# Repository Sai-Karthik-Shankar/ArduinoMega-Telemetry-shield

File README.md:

# ArduinoMega-Telemetry-shield

## Description
A simple datalogger with an Arduino mega at the heart of it, and a modular plate where inexpensive off the shelf modules for various purposes can be mounted.

## Capabilites
- 3-axis Acceleration
- 3-axis Gyroscope
- 3-axis Magnetometer
- GPS Location sensor
- 2 Channel Frequency inputs
- Bluetooth
- WiFi tethering
- Realtime Storage in Particle Photon Cloud
- Serial output to Nextion Display Module

## Additionals
Bluetooth Datalogger mobile application can interface with the ESP8266 and store the data collected in a sorted CSV file at the selected baud-rate.

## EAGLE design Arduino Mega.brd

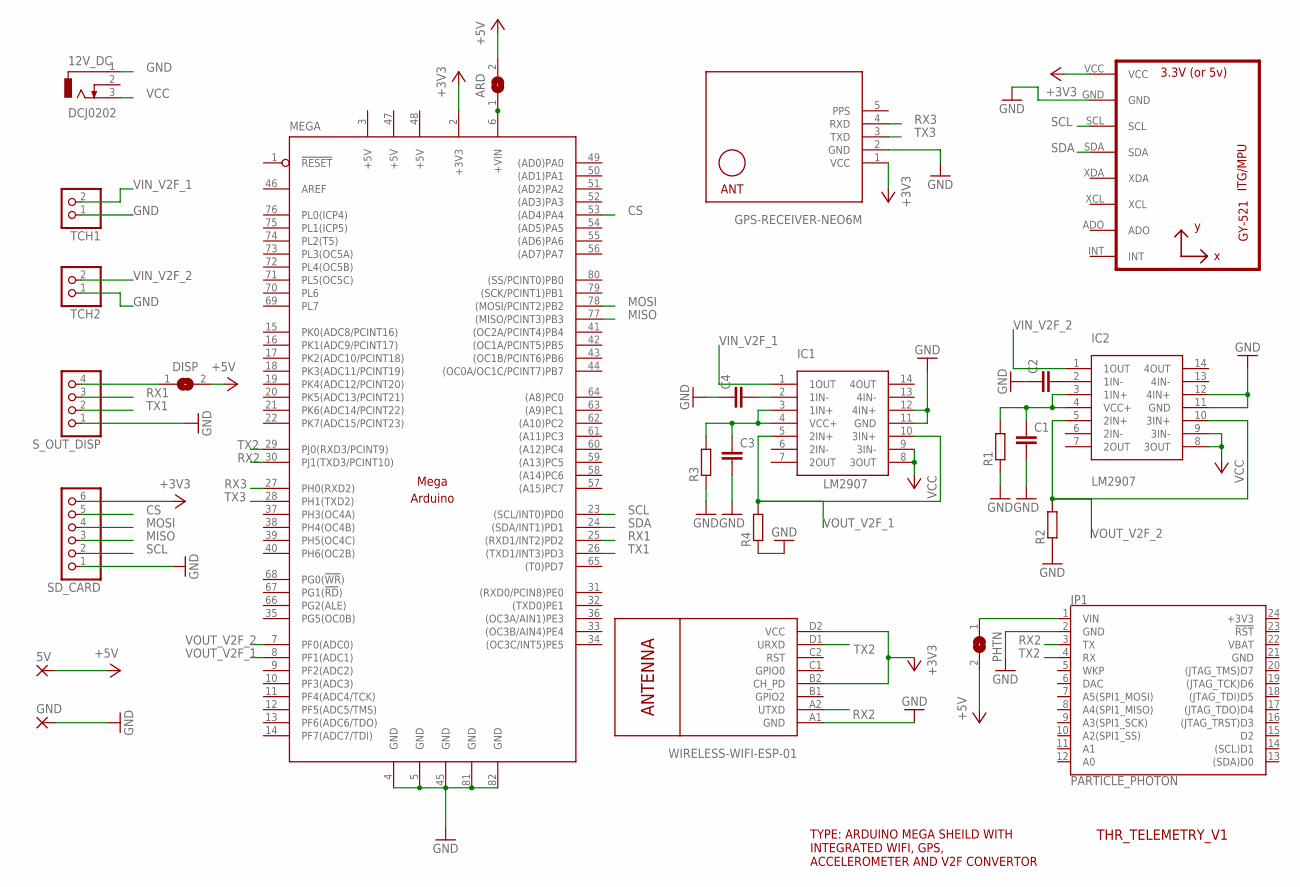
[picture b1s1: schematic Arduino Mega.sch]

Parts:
5V: WIREPADSMD5-2,5; 5-2,5
12V_DC: DCJ0202
ARD: SJ
C1, C2, C3, C4: C-EUC0805; C0805
DISP: SJ
GND: WIREPADSMD5-2,5; 5-2,5
IC1, IC2: LM2907; 14-SOIC
JP1: PARTICLE_PHOTON
MEGA: MEGAARDUINO_11; MEGA_ARDUINO_1
PHTN: SJ
R1, R2, R3, R4: R-EU_R0805; R0805
SD_CARD: PINHD-1X6; 1X06
S_OUT_DISP: PINHD-1X4; 1X04
TCH1, TCH2: PINHD-1X2; 1X02
U1: GY-521MPU6050; GY-521
U$1: GPS-RECEIVER-NEO6M
U$2: WIRELESS-WIFI-ESP-01

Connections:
+3V3: JP1.24 (+3V3), MEGA.2 (+3V3), SD_CARD.6, U1.VCC, U$1.1 (VCC), U$2.B2 (CH_PD), U$2.D2 (VCC)
+5V: 5V.1, ARD.2, DISP.2, MEGA.3 (+5V), MEGA.47 (+5V), MEGA.48 (+5V), PHTN.2
CS: MEGA.53 ((AD4)PA4), SD_CARD.5
GND: 12V_DC.1, C1.2, C2.1, C3.2, C4.1, GND.1, IC1.11 (GND), IC1.12 (4IN+), IC2.11 (GND), IC2.12 (4IN+), JP1.2 (GND), JP1.21 (GND), MEGA.4 (GND), MEGA.5 (GND), MEGA.45 (GND), MEGA.81 (GND), MEGA.82 (GND), R1.1, R2.1, R3.1, R4.1, SD_CARD.1, S_OUT_DISP.1, TCH1.1, TCH2.1, U1.GND, U$1.2 (GND), U$2.A1 (GND)
MISO: MEGA.77 ((MISO/PCINT3)PB3), SD_CARD.3
MOSI: MEGA.78 ((MOSI/PCINT2)PB2), SD_CARD.4
unnamed: C2.2, IC2.2 (1IN-)
unnamed: C1.1, IC2.3 (1IN+), IC2.4 (VCC+), R1.2
unnamed: ARD.1, MEGA.6 (+VIN)
unnamed: JP1.1 (VIN), PHTN.1
unnamed: C4.2, IC1.2 (1IN-)
unnamed: DISP.1, S_OUT_DISP.4
unnamed: C3.1, IC1.3 (1IN+), IC1.4 (VCC+), R3.2
PPS: U$1.5 (PPS)
RX1: MEGA.25 ((RXD1/INT2)PD2), S_OUT_DISP.3
RX2: JP1.3 (TX), MEGA.30 (PJ1(TXD3/PCINT10)), U$2.A2 (UTXD)
RX3: MEGA.27 (PH0(RXD2)), U$1.4 (RXD)
SCL: MEGA.23 ((SCL/INT0)PD0), SD_CARD.2, U1.SCL
SDA: MEGA.24 ((SDA/INT1)PD1), U1.SDA
TX1: MEGA.26 ((TXD1/INT3)PD3), S_OUT_DISP.2
TX2: JP1.4 (RX), MEGA.29 (PJ0(RXD3/PCINT9)), U$2.D1 (URXD)
TX3: MEGA.28 (PH1(TXD2)), U$1.3 (TXD)
VBAT: JP1.22 (VBAT)
VCC: 12V_DC.3, IC1.8 (3OUT), IC1.9 (3IN-), IC2.8 (3OUT), IC2.9 (3IN-)
VIN_V2F_1: IC1.1 (1OUT), TCH1.2
VIN_V2F_2: IC2.1 (1OUT), TCH2.2
VOUT_V2F_1: IC1.5 (2IN+), IC1.10 (3IN+), MEGA.8 (PF1(ADC1)), R4.2
VOUT_V2F_2: IC2.5 (2IN+), IC2.10 (3IN+), MEGA.7 (PF0(ADC0)), R2.2

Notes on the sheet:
THR_TELEMETRY_V1
TYPE: ARDUINO MEGA SHEILD WITH INTEGRATED WIFI, GPS, ACCELEROMETER AND V2F CONVERTOR

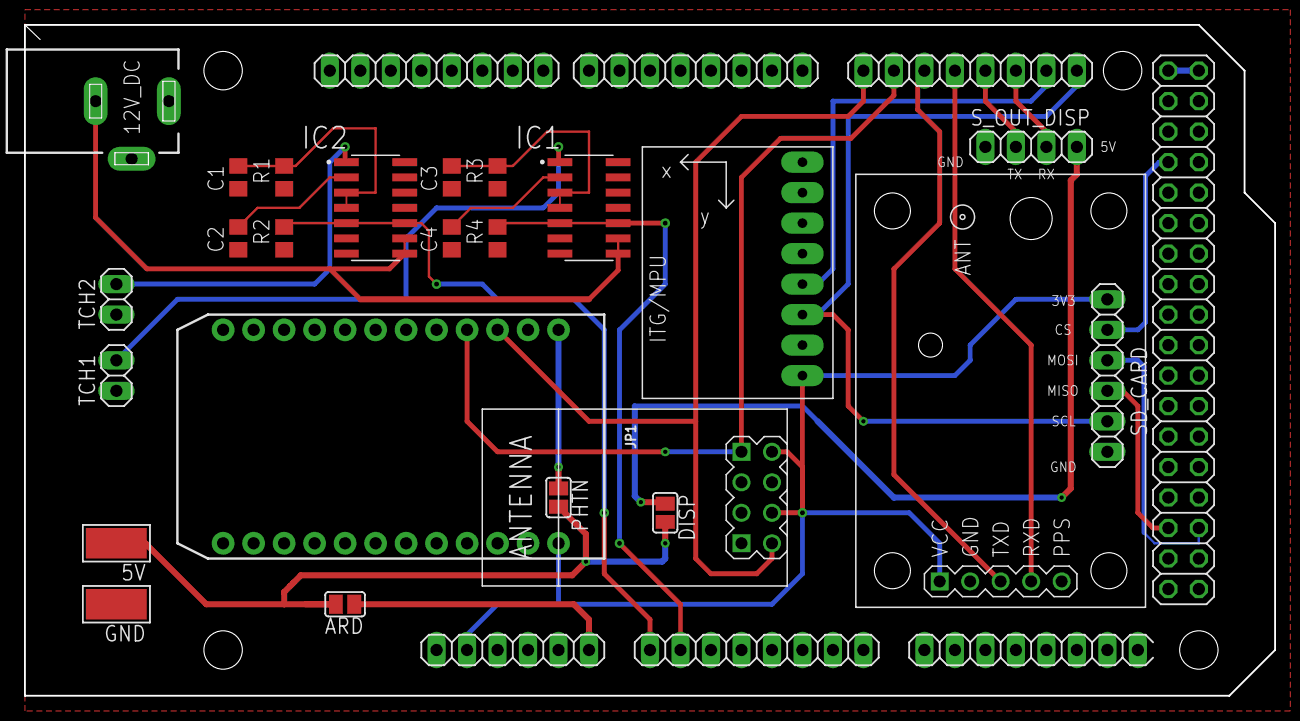
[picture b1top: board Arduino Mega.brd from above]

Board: 2 copper layers, 104.1 x 55.9 mm, 25 parts (0 on the bottom side), 26 nets.

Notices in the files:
parts and their libraries:
neo 6m: Released under the Creative Commons Attribution 4.0 International License: http://creativecommons.org/licenses/by/4.0
SparkFun-Boards: Licensing: Creative Commons ShareAlike 4.0 International - https://creativecommons.org/licenses/by-sa/4.0
